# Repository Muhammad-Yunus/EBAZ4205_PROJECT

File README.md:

# EBAZ4205 PROJECT
*EBAZ4205 (Zynq-7010) projects — from PYNQ & Vivado designs to Xilinx SDK apps and custom expansion board PCB.*
- 📄 Install Board Files EBAZ4205 in Vivado, 👉 [Board Files](https://github.com/Muhammad-Yunus/EBAZ4205_Vivado/tree/main/Documents/Board%20files)
- 💿 Download PYNQ OS for EBAZ4205 from, 👉 [Release Page](https://github.com/Muhammad-Yunus/EBAZ4205_PROJECT/releases/tag/v1.0)
- 📁 Follow PYNQ tutorial in `PYNQ/` folder.
- 📄 Datasheet :
     - You can download or view the datasheet here 👉 [EBAZ4205 Datasheet PDF](/resource/ebaz4205_schematic.pdf)

### EBAZ4205 Pinout

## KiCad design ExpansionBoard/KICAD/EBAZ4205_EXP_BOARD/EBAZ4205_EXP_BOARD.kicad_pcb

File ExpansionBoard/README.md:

# EBAZ4205 Expansion Board
<br><br>
<br><br>

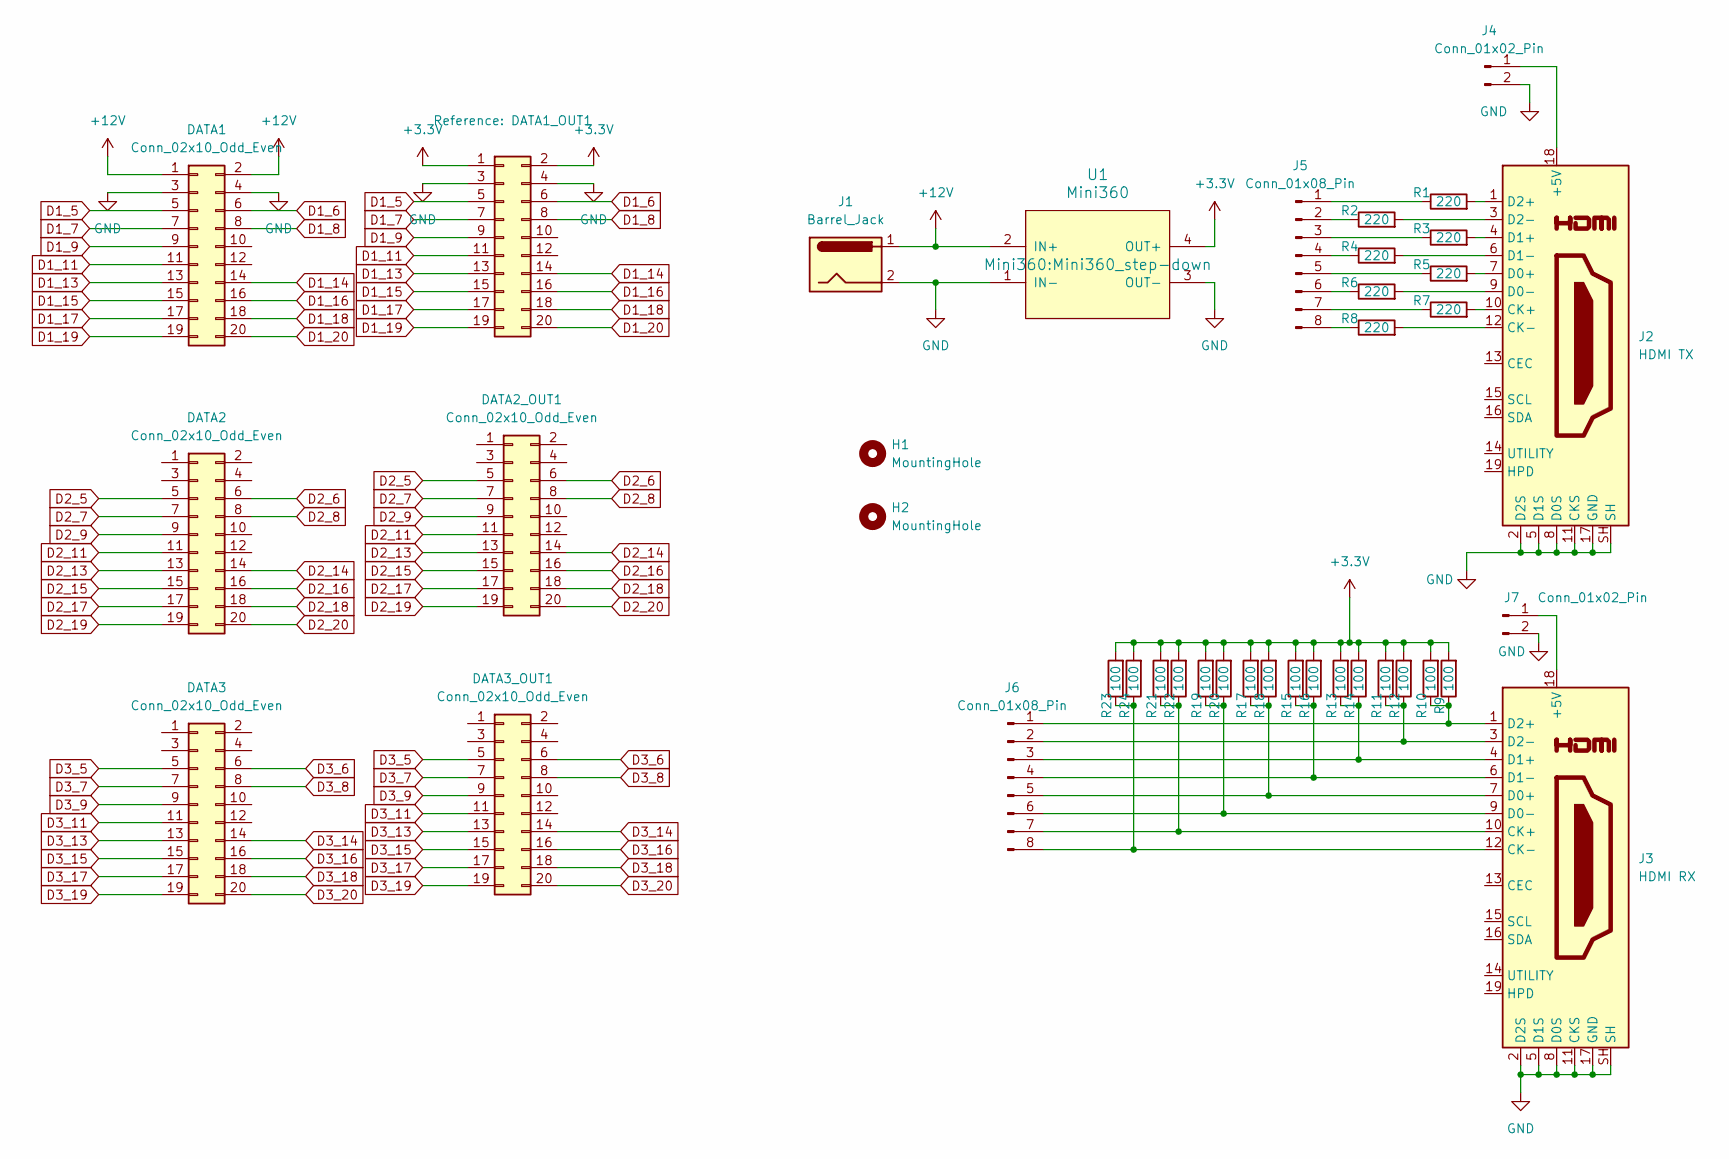
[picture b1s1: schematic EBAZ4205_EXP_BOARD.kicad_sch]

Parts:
DATA1, DATA2, DATA3: Conn_02x10_Odd_Even; CardEdge_2x10_P2.00mm_TopBottom_Separated
DATA1_OUT1, DATA2_OUT1, DATA3_OUT1: Conn_02x10_Odd_Even; PinSocket_2x10_P2.54mm_Vertical
H1, H2: MountingHole; MountingHole_3.2mm_M3_Pad
J1: Barrel_Jack; BarrelJack_Horizontal
J2: HDMI TX; HDMI_A_Molex_208658-1001_Horizontal
J3: HDMI RX; HDMI_A_Molex_208658-1001_Horizontal
J4, J7: Conn_01x02_Pin; PinHeader_1x02_P2.54mm_Vertical
J5, J6: Conn_01x08_Pin; PinHeader_1x08_P2.54mm_Vertical
R1, R2, R3, R4, R5, R6, R7, R8: 220; R_0402_1005Metric_Pad0.72x0.64mm_HandSolder
R9, R10, R11, R12, R13, R14, R15, R16, R17, R18, R19, R20, R21, R22, R23, R24: 100; R_0402_1005Metric_Pad0.72x0.64mm_HandSolder
U1: Mini360; Mini360_step-down

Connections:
+3.3V: DATA1_OUT1.1, DATA1_OUT1.2, R9.2, R10.2, R11.2, R12.2, R13.2, R14.2, R15.2, R16.2, R17.2, R18.2, R19.2, R20.2, R21.2, R22.2, R23.2, R24.2, U1.4 (OUT+)
+12V: DATA1.1, DATA1.2, J1.1, U1.2 (IN+)
D1_5: DATA1.5, DATA1_OUT1.5
D1_6: DATA1.6, DATA1_OUT1.6
D1_7: DATA1.7, DATA1_OUT1.7
D1_8: DATA1.8, DATA1_OUT1.8
D1_9: DATA1.9, DATA1_OUT1.9
D1_11: DATA1.11, DATA1_OUT1.11
D1_13: DATA1.13, DATA1_OUT1.13
D1_14: DATA1.14, DATA1_OUT1.14
D1_15: DATA1.15, DATA1_OUT1.15
D1_16: DATA1.16, DATA1_OUT1.16
D1_17: DATA1.17, DATA1_OUT1.17
D1_18: DATA1.18, DATA1_OUT1.18
D1_19: DATA1.19, DATA1_OUT1.19
D1_20: DATA1.20, DATA1_OUT1.20
D2_5: DATA2.5, DATA2_OUT1.5
D2_6: DATA2.6, DATA2_OUT1.6
D2_7: DATA2.7, DATA2_OUT1.7
D2_8: DATA2.8, DATA2_OUT1.8
D2_9: DATA2.9, DATA2_OUT1.9
D2_11: DATA2.11, DATA2_OUT1.11
D2_13: DATA2.13, DATA2_OUT1.13
D2_14: DATA2.14, DATA2_OUT1.14
D2_15: DATA2.15, DATA2_OUT1.15
D2_16: DATA2.16, DATA2_OUT1.16
D2_17: DATA2.17, DATA2_OUT1.17
D2_18: DATA2.18, DATA2_OUT1.18
D2_19: DATA2.19, DATA2_OUT1.19
D2_20: DATA2.20, DATA2_OUT1.20
D3_5: DATA3.5, DATA3_OUT1.5
D3_6: DATA3.6, DATA3_OUT1.6
D3_7: DATA3.7, DATA3_OUT1.7
D3_8: DATA3.8, DATA3_OUT1.8
D3_9: DATA3.9, DATA3_OUT1.9
D3_11: DATA3.11, DATA3_OUT1.11
D3_13: DATA3.13, DATA3_OUT1.13
D3_14: DATA3.14, DATA3_OUT1.14
D3_15: DATA3.15, DATA3_OUT1.15
D3_16: DATA3.16, DATA3_OUT1.16
D3_17: DATA3.17, DATA3_OUT1.17
D3_18: DATA3.18, DATA3_OUT1.18
D3_19: DATA3.19, DATA3_OUT1.19
D3_20: DATA3.20, DATA3_OUT1.20
GND: DATA1.3, DATA1.4, DATA1_OUT1.3, DATA1_OUT1.4, J1.2, J2.2 (D2S), J2.5 (D1S), J2.8 (D0S), J2.11 (CKS), J2.17 (GND), J2.SH, J3.2 (D2S), J3.5 (D1S), J3.8 (D0S), J3.11 (CKS), J3.17 (GND), J3.SH, J4.2, J7.2, U1.1 (IN-), U1.3 (OUT-)
unnamed: J2.18 (+5V), J4.1
unnamed: J2.10 (CK+), R7.2
unnamed: J2.12 (CK-), R8.2
unnamed: J2.7 (D0+), R5.2
unnamed: J2.9 (D0-), R6.2
unnamed: J2.4 (D1+), R3.2
unnamed: J2.6 (D1-), R4.2
unnamed: J2.1 (D2+), R1.2
unnamed: J2.3 (D2-), R2.2
unnamed: J3.18 (+5V), J7.1
unnamed: J3.10 (CK+), J6.7, R21.1, R22.1
unnamed: J3.12 (CK-), J6.8, R23.1, R24.1
unnamed: J3.7 (D0+), J6.5, R17.1, R18.1
unnamed: J3.9 (D0-), J6.6, R19.1, R20.1
unnamed: J3.4 (D1+), J6.3, R13.1, R14.1
unnamed: J3.6 (D1-), J6.4, R15.1, R16.1
unnamed: J3.1 (D2+), J6.1, R9.1, R10.1
unnamed: J3.3 (D2-), J6.2, R11.1, R12.1
unnamed: J5.1, R1.1
unnamed: J5.2, R2.1
unnamed: J5.3, R3.1
unnamed: J5.4, R4.1
unnamed: J5.5, R5.1
unnamed: J5.6, R6.1
unnamed: J5.7, R7.1
unnamed: J5.8, R8.1

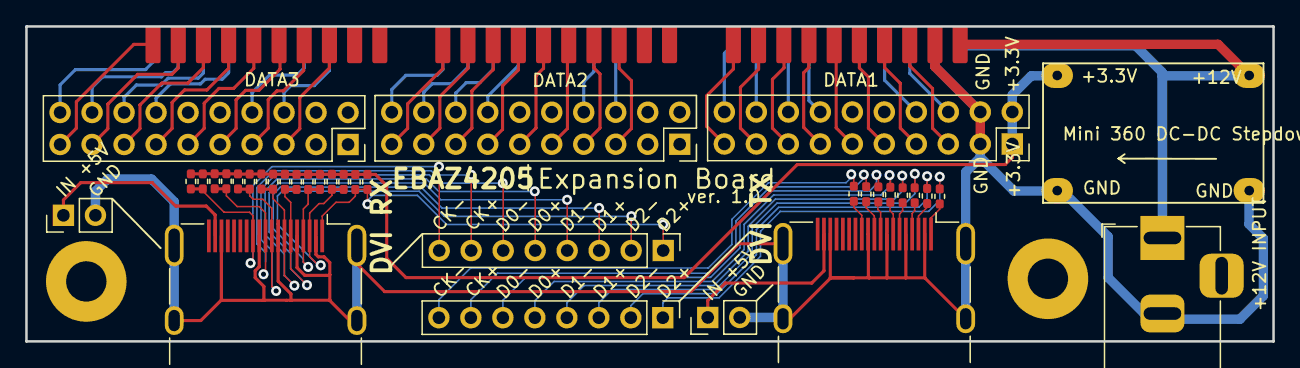
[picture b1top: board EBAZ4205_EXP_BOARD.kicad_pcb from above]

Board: 2 copper layers, 99.0 x 25.0 mm, 40 parts (0 on the bottom side), 71 nets.

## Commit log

2025-08-16 Add PYNQ overlays, Vivado TCL scripts, and documentation for EBAZ4205
    - Added PYNQ notebooks and overlays for PS and AXI GPIO examples
    - Included Vivado TCL scripts and project files for both overlays
    - Added resource files: pinout image and schematic PDF
    - Updated main README and added documentation for new components
    - Added XilinxSDK README
2025-08-16 update Pinout image
2025-08-17 add constraints file for Vivado projects
2025-08-17 add axi i2c and oled ssd1306 128x32 demo
2025-08-17 add constraints file for AxiI2C vivado project
2025-08-17 add project info in README.md
2025-08-17 add some image resource for AxiGPIO demo
2025-08-17 minor fix for image path in README.md
2025-08-17 add some image resources for AxiGPIO Demo
2025-08-17 adding expansion board project files
2025-08-17 fix minor typos and add some details to the README files
2025-08-17 fixing some documentation issues
2025-08-17 fixing typo in notebook
2025-08-17 add some documentation to EBAZ4205_2_AXIGPIO.ipynb
2025-08-22 add AXIQuadSPI demo
2025-08-22 add contraint file for AXIQuadSPI and vivado project instructions
2025-08-24 add Xilinx SDK Applocation Project for AXI Quad SPI + SPI TFT LCD ST7735 + LVGL Demo
2025-08-24 update build instruction for TFT LCD with LVGL library
2025-08-24 fixing some typos and formatting
2025-08-24 resize image size in README.md
2025-08-24 uodate some documentation
2025-08-24 Adding LVGL + TFT LCD ILI9341 example for EBAZ4205 board with 4-AxiQuadSPI IP
2025-08-24 update README.md for LVGL Demo Music Player on ILI9341 LCD
2025-09-07 Adding DVI TPG Project in Vivado and Xilinx SDK
2025-09-07 fixing some typos
2025-09-07 add application code
2025-09-14 Refactor project structure
2025-09-14 fixing typos and updating project references
2025-09-14 add XilinxSDK PS example (TODO)
2025-09-14 add XilinxSDK TODO
2025-09-14 fixing instructions for SPI_LCD_ILI9341_LVGL project
2025-09-14 add HDMI Passthrough design for EBAZ4205 board
2025-09-14 update README.md for HDMI Passthrough in Xilinx SDK
2025-09-14 change image size
2025-09-21 add documentation for 7_AD9226_ADC project
2025-09-21 add XilinxSDK/7_AD9226_ADC/README.md and XilinxSDK/7_AD9226_ADC/src/* files
2025-09-21 update README.md and add Python FFT client app
2025-09-21 udpate README.md
